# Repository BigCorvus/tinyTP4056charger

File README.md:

# tinyTP4056charger
Tiny TP4056 lithium charger without micro USB. This has to be connected externally to save space and include in your smallest projects that require lithium charging.

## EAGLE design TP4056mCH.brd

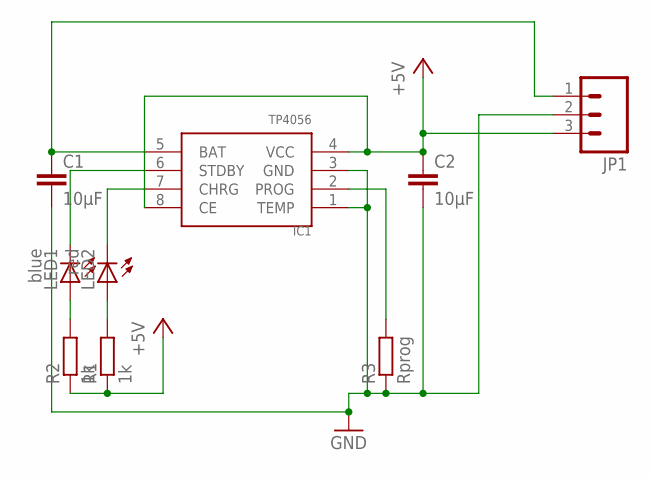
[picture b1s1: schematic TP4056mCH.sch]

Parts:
C1, C2: 10µF; C0805
IC1: TP4056; SOP-8
JP1: M03PTH; 1X03
LED1: blue; CHIP-LED0805
LED2: red; CHIP-LED0805
R1, R2: 1k; R0603
R3: Rprog; R0603

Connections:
+5V: C2.1, IC1.4 (VCC), IC1.8 (CE), JP1.3, R1.1, R2.1
GND: C1.2, C2.2, IC1.1 (TEMP), IC1.3 (GND), JP1.2, R3.1
unnamed: IC1.2 (PROG), R3.2
unnamed: C1.1, IC1.5 (BAT), JP1.1
unnamed: IC1.6 (STDBY), LED1.C
unnamed: IC1.7 (CHRG), LED2.C
unnamed: LED1.A, R2.2
unnamed: LED2.A, R1.2

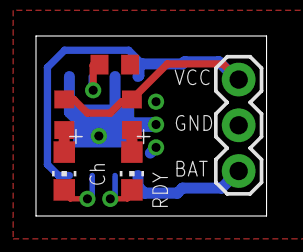
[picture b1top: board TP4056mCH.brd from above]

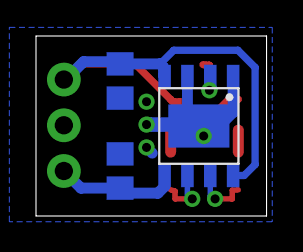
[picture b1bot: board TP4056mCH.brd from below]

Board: 2 copper layers, 12.8 x 10.0 mm, 9 parts (3 on the bottom side), 8 nets.

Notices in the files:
parts and their libraries:
SparkFun-Connectors: Licensing: Creative Commons ShareAlike 4.0 International - https://creativecommons.org/licenses/by-sa/4.0
